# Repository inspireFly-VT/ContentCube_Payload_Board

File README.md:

View this project on [CADLAB.io](https://cadlab.io/project/28566). 

# ContentCube_Payload_Board
The payload board for inspireFly's ContentCube satellite.

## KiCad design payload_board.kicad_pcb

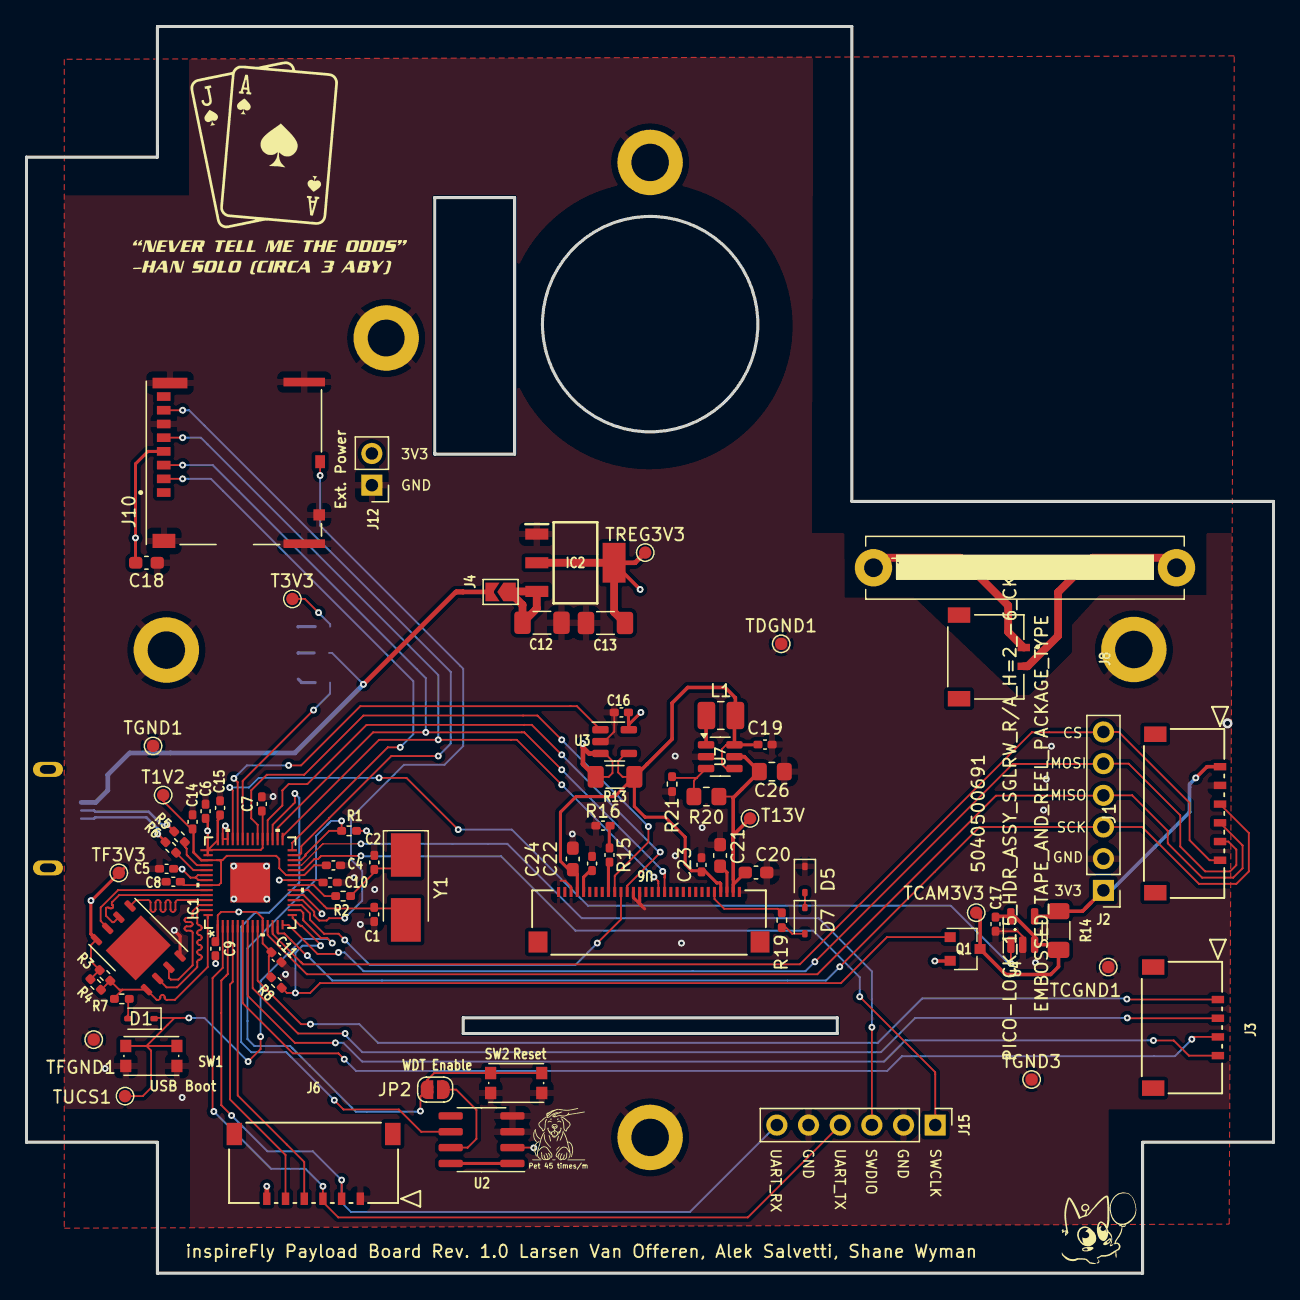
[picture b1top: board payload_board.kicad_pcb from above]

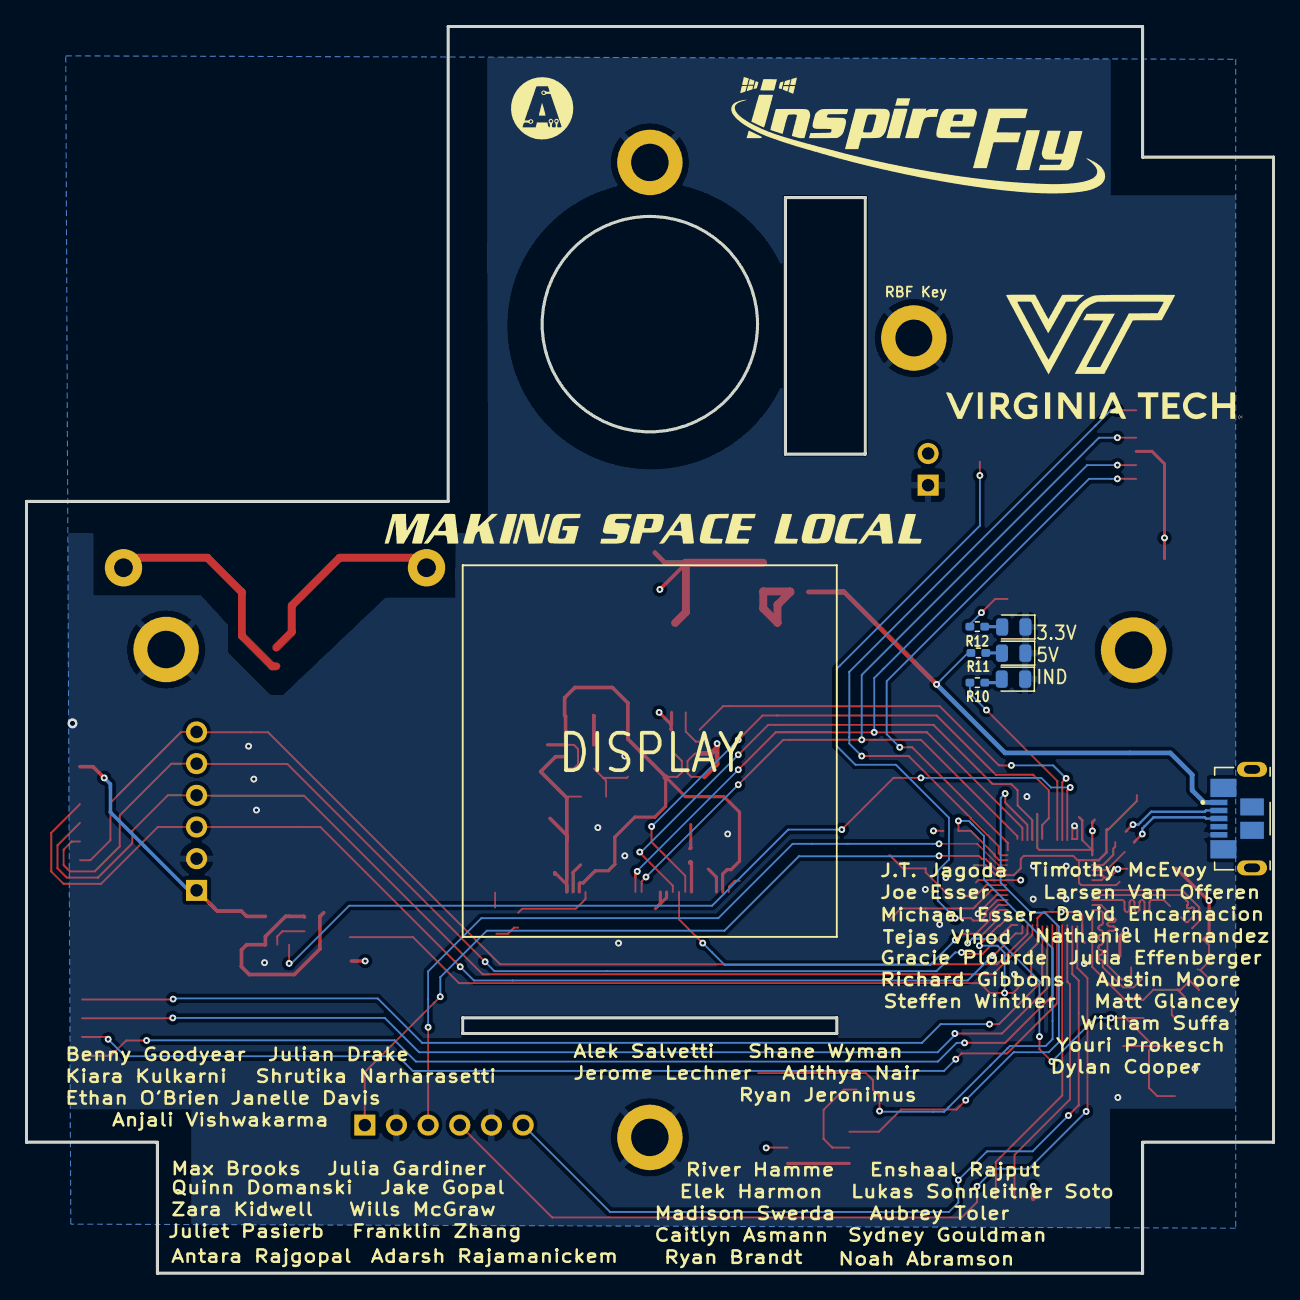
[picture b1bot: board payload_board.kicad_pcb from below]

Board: 4 copper layers, 100.0 x 100.0 mm, 86 parts (8 on the bottom side), 66 nets.

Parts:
C1, C2: 27pF; C_0402_1005Metric_Pad0.74x0.62mm_HandSolder
C4, C5, C7, C8, C9, C10, C11, C15, C16, C17: 0.1uF; C_0402_1005Metric_Pad0.74x0.62mm_HandSolder
C6, C14, C19: 1uF; C_0402_1005Metric_Pad0.74x0.62mm_HandSolder
C12: 10uF; C_1206_3216Metric_Pad1.33x1.80mm_HandSolder
C13: 22uF; C_1206_3216Metric_Pad1.33x1.80mm_HandSolder
C18, C24: 10uF; C_0603_1608Metric_Pad1.08x0.95mm_HandSolder
C20, C21: 10uF/16V; C_0603_1608Metric_Pad1.08x0.95mm_HandSolder
C22, C23: 1.0uF; C_0402_1005Metric_Pad0.74x0.62mm_HandSolder
C26: 4.7uF; R_0805_2012Metric_Pad1.20x1.40mm_HandSolder
D1, D5, D7: NSR0320; D_SOD-323
D2, D3, D4: LED; LED_0805_2012Metric
IC1: RP2040_QFN56; custom_IC57_RP2040
IC2: AZ1117CH-3.3TRG1; SOT230P700X180-4N
J1: Cam_PicoLock; Molex_Pico_CON_5040500691
J2: Cam_Conn; PinHeader_1x06_P2.54mm_Vertical
J2#2, J5: MountingHoles
J3: Antenna_Conn; Molex_Pico_CON_5040500491
J4: usb jumper; SolderJumper-2_P1.3mm_Open_TrianglePad1.0x1.5mm
J6: Breakout; Molex_Pico_CON_5040500691
J7: Molex_Micro_USB; MOLEX_105164-0001
J8: FC to EPS Connector; MOLEX_504050-0291
J10: 503398-1892; MOLEX_503398-1892
J12: FC Breakout; PinHeader_1x02_P2.54mm_Vertical
J15: SWC; PinHeader_1x06_P2.54mm_Vertical
JP2: SolderJumper_2_Open; SolderJumper-2_P1.3mm_Open_RoundedPad1.0x1.5mm
L1: 10uH/1A; L_1008_2520Metric_Pad1.43x2.20mm_HandSolder
Q1: Q_PMOS_GSD; SC-59
R1, R3, R8: 10k; R_0402_1005Metric_Pad0.72x0.64mm_HandSolder
R2, R7: 1K; R_0402_1005Metric_Pad0.72x0.64mm_HandSolder
R4: DNF; R_0402_1005Metric_Pad0.72x0.64mm_HandSolder
R5, R6: 27.4; R_0402_1005Metric_Pad0.72x0.64mm_HandSolder
R10, R12: 220; R_0402_1005Metric_Pad0.72x0.64mm_HandSolder
R11: 470; R_0402_1005Metric_Pad0.72x0.64mm_HandSolder
R13, R14: 0.065; R_1206_3216Metric_Pad1.30x1.75mm_HandSolder
R15, R16: 300k; C_0402_1005Metric_Pad0.74x0.62mm_HandSolder
R19: 50; R_0402_1005Metric_Pad0.72x0.64mm_HandSolder
R20: 16k; R_0805_2012Metric_Pad1.20x1.40mm_HandSolder
R21: 1k; R_0402_1005Metric_Pad0.72x0.64mm_HandSolder
SW1, SW2: KMR2; SW_Push_1P1T_NO_CK_KMR2
T1V2, T3V3, T13V: TESTPOINTROUND1.5MMNO; TestPoint_Pad_D1.0mm
TCAM3V3: TESTPOINTROUND1.5MMNO; TestPoint_Pad_D1.0mm
TCGND1: TESTPOINTROUND1.5MMNO; TestPoint_Pad_D1.0mm
TDGND1: TESTPOINTROUND1.5MMNO; TestPoint_Pad_D1.0mm
TF3V3: TESTPOINTROUND1.5MMNO; TestPoint_Pad_D1.0mm
TFGND1: TESTPOINTROUND1.5MMNO; TestPoint_Pad_D1.0mm
TGND1, TGND3: TESTPOINTROUND1.5MMNO; TestPoint_Pad_D1.0mm
TREG3V3: TESTPOINTROUND1.5MMNO; TestPoint_Pad_D1.0mm
TUCS1: TESTPOINTROUND1.5MMNO; TestPoint_Pad_D1.0mm
U1: W25Q128JVPIQ TR; WDFN-8-1EP_6x5mm_P1.27mm_EP3.4x4mm
U2: MAX706RESA; SOIC-8_3.9x4.9mm_P1.27mm
U3, U4: INA180A3; SOT-23-5
U6: CON30_1X30_DRB_XF2C_TYC
U7: TLV61046ADB; SOT-23-6
Y1: ABLS-12.000MHZ-B2-T; Crystal_SMD_5032-2Pin_5.0x3.2mm_HandSoldering

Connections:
1.2V: C4.2, C5.2, C14.2, IC1.23 (DVDD), IC1.45 (VREG_VOUT), IC1.50 (DVDD), T1V2.1
+3.3V: C6.2, C7.1, C8.1, C9.1, C10.1, C11.1, C13.1, C15.1, C16.1, C18.2, IC1.1 (IOVDD), IC1.10 (IOVDD), IC1.22 (IOVDD), IC1.33 (IOVDD), IC1.42 (IOVDD), IC1.43 (ADC_IOVDD), IC1.44 (VREG_IOVDD), IC1.48 (USB_IOVDD), IC1.49 (IOVDD), IC2.2 (OUTPUT), IC2.4 (VOUT), J6.6, J10.4 (VDD), J12.2, Q1.2 (S), R1.1, R3.1, R4.2, R8.2, R12.2, R13.2, T3V3.1, TF3V3.1, TREG3V3.1, U1.8 (VCC), U2.2 (VCC), U3.3 (+), U3.5 (V+)
+13V: C20.2, C26.2, R20.1, T13V.1, U6.P$29 (VCC), U7.5 (VOUT)
/D+: J7.3 (D+), R6.1
/D-: J7.2 (D-), R5.2
/QSPI_CS: IC1.56 (~QSPI_CS), R3.2, R4.1, R7.1, U1.1 (SSEL)
/QSPI_DATA[0]: IC1.53 (QSPI_SD0), U1.5 (MOSI)
/QSPI_DATA[1]: IC1.55 (QSPI_SD1), U1.2 (MISO)
/QSPI_DATA[2]: IC1.54 (QSPI_SD2), U1.3 (WP#/IO2)
/QSPI_DATA[3]: IC1.51 (QSPI_SD3), U1.7 (HOLD#/IO3)
/QSPI_SCK: IC1.52 (QSPI_SCLK), U1.6 (SCK)
/USBBOOT: D1.1 (C), IC1.16 (GPIO13), SW1.1, TUCS1.1
/~RESET: IC1.26 (/RUN), JP2.2 (B), R1.2, SW2.1
ADC0: IC1.38 (GPIO26/AD0), U3.1
ADC1: IC1.39 (GPIO27/AD1), U4.1
BURN_A: IC1.8 (GPIO6), J3.2
BURN_B: IC1.9 (GPIO7), J3.1
Break_SCL: IC1.5 (GPIO3), J6.4
Break_SDA: IC1.4 (GPIO2), J6.5
CIN-: J1.1, J2.1, R14.2, U4.4 (-)
Cam_3.3v: C17.2, Q1.3 (D), R14.1, TCAM3V3.1, U4.3 (+), U4.5 (V+)
Cam_RST: IC1.15 (GPIO12), Q1.1 (G), R8.1
DIN-: C19.2, C23.2, C24.2, L1.1, R13.1, U3.4 (-), U6.P$4 (VCI), U6.P$27 (VDDIO), U7.4 (EN), U7.6 (VI)
Disp_DC: IC1.17 (GPIO14), U6.P$11 (D/C#)
Disp_RST: IC1.34 (GPIO22), U6.P$10 (RES#)
GND: C1.1, C2.1, C4.1, C5.1, C6.1, C7.2, C8.2, C9.2, C10.2, C11.2, C12.2, C13.2, C14.1, C15.2, C16.2, C17.1, C18.1, C19.1, C20.1, C21.1, C22.1, C23.1, C24.1, C26.1, D2.1 (K), D3.1 (K), D4.1 (K), D5.1 (C), IC1.19 (TESTEN), IC1.40 (GPIO28/AD2), IC1.41 (GPIO29/AD3), IC1.57, IC2.1 (ADJ/GND), J1.2, J2.2, J2#2.1 (VTref), J5.1, J6.1, J7.5 (GND), J10.6 (VSS), J10.9 (VSS__1), J10.P1 (SHIELD), J10.P2 (SHIELD__1), J10.P3 (SHIELD__2), J10.P4 (SHIELD__3), J12.1, J15.2, J15.5, R16.1, R21.2, SW1.2 (S), SW2.2 (S1), TCGND1.1, TDGND1.1, TFGND1.1, TGND1.1, TGND3.1, U1.4 (VSS), U2.3 (GND), U2.4 (PFI), U3.2 (GND), U4.2 (GND), U6.P$1 (NC(GND)@2), U6.P$3 (VSS), U6.P$13 (BS1), U6.P$14 (BS0), U6.P$30 (NC(GND)@1), U7.2 (GND)
I2C1_SCL: IC1.7 (GPIO5), J3.4
I2C1_SDA: IC1.6 (GPIO4), J3.3
unnamed: C2.2, R2.1, Y1.1
unnamed: D1.2 (A), R7.2
unnamed: D2.2 (A), R10.1
unnamed: D3.2 (A), R11.1
unnamed: D4.2 (A), R12.1
unnamed: D5.2 (A), D7.1 (C)
unnamed: D7.2 (A), R19.1
unnamed: IC1.37 (GPIO25), R10.2
unnamed: IC1.47 (USB_D+), R6.2
unnamed: IC1.46 (USB_D-), R5.1
unnamed: C1.2, IC1.20 (XIN), Y1.2
unnamed: IC1.21 (XOUT), R2.2
unnamed: JP2.1 (A), U2.7 (~RESET)
unnamed: R15.1, R16.2
unnamed: U2.1 (~MR), U2.8 (~WDO)
unnamed: R15.2, U6.P$9 (IREF)
unnamed: C21.2, U6.P$28 (VCOMH)
unnamed: C22.2, U6.P$5 (VDD)
unnamed: R19.2, U6.P$26 (VSL)
unnamed: R20.2, R21.1, U7.3 (FB)
unnamed: L1.2, U7.1 (SW)
SD_IND: IC1.18 (GPIO15), J10.10 (DETECT_SWITCH)
SPI0_CS_DISP: IC1.32 (GPIO21), U6.P$12 (CS#)
SPI0_CS_SD: IC1.28 (GPIO17), J10.2 (CD/DAT3^2)
SPI0_MISO: IC1.27 (GPIO16), J10.7 (DAT0)
SPI0_MOSI: IC1.30 (GPIO19), J10.3 (CMD), U6.P$18 (D1/SDIN)
SPI0_SCK: IC1.29 (GPIO18), J10.5 (CLK), U6.P$17 (D0/SCK)
SPI1_CS_Cam: IC1.12 (GPIO9), J1.6, J2.6
SPI1_MISO_Cam: IC1.11 (GPIO8), J1.4, J2.4
SPI1_MOSI_Cam: IC1.14 (GPIO11), J1.5, J2.5
SPI1_SCK_Cam: IC1.13 (GPIO10), J1.3, J2.3
SWCLK: IC1.24 (SWCLK), J15.1
SWDIO: IC1.25 (SWDIO), J15.3
UART1_RX: IC1.3 (GPIO1), J6.2, J15.6
UART1_TX: IC1.2 (GPIO0), J6.3, J15.4
VBUS: J4.2 (B), J7.1 (VBUS), R11.2
VUR: C12.1, IC2.3 (INPUT), J4.1 (A)
WDT_WDI: IC1.31 (GPIO20), U2.6 (~WDI)

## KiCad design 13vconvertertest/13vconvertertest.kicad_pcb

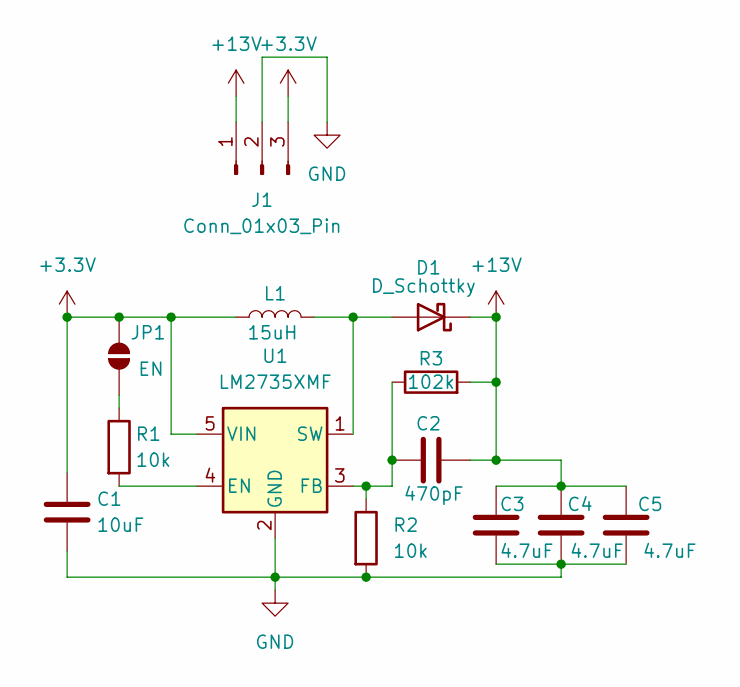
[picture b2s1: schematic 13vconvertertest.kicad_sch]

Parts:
C1: 10uF; C_0402_1005Metric
C2: 470pF; C_0805_2012Metric
C3, C4, C5: 4.7uF; C_0603_1608Metric
D1: D_Schottky; D_SOD-123F
J1: Conn_01x03_Pin; PinHeader_1x03_P1.00mm_Vertical
JP1: EN; SolderJumper-2_P1.3mm_Open_TrianglePad1.0x1.5mm
L1: 15uH; L_Bourns-SRU1028_10.0x10.0mm
R1, R2: 10k; R_0805_2012Metric
R3: 102k; R_0402_1005Metric
U1: LM2735XMF; SOT-23-5

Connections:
+3.3V: C1.1, J1.3, JP1.2 (B), L1.1, U1.5 (VIN)
+13V: C2.2, C3.1, C4.1, C5.1, D1.1 (K), J1.1, R3.2
GND: C1.2, C3.2, C4.2, C5.2, J1.2, R2.2, U1.2 (GND)
unnamed: D1.2 (A), L1.2, U1.1 (SW)
unnamed: JP1.1 (A), R1.1
unnamed: R1.2, U1.4 (EN)
unnamed: C2.1, R2.1, R3.1, U1.3 (FB)

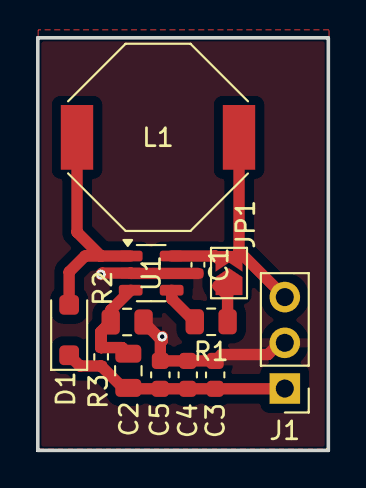
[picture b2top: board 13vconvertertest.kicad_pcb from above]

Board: 2 copper layers, 16.1 x 22.9 mm, 13 parts (0 on the bottom side), 7 nets.

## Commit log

2024-10-15 Port from CADLAB to Github
2024-10-15 Backlink to CADLAB.io has been added.
2024-10-16 Updated component placements and footprints
2024-10-17 Updated display footprints to reflect avaliability
2024-10-19 Changed the orientation of the connector to align, and moved a couple of the components Will continue tomorrow
2024-10-19 Forgot to save changes for schematic
2024-10-19 Rotated it back (by bad i dont know how to read schematics) and added some connections
2024-10-19 Connected some more stuff
2024-10-20 Moved the sd card on the board
2024-10-20 oops, forgot to connect some of the gnd pins
2024-10-20 Some of the planes where unconnected
2024-10-20 Moved some of the traces further appart
2024-10-20 A little more
2024-10-20 Final move
2024-10-20 moved some of the silkcreen labels
2024-10-20 Moved some line appart
2024-10-20 Inventory of the components
2024-10-23 Fixed RP2040 connections and changed sd card
2024-10-23 changed footprint for sd card and fixed not gnd planes
2024-10-23 Fixed some errors and added manufactering file
2024-10-25 Update BOM and part identifiers on PCB
2024-10-26 Updated inventory (payload_board.xlsx)
2024-10-27 Updated footprints
2024-10-28 Finalized part selection and gbr for 073 manufacturing.
2024-10-31 Flipped the outline and moved the screen and some of the connectors Now the front in Kicad is the back in the satelite (inside) and vice versa
2024-11-01 Moved the final connector from back to front, footprint kepout for chasis mounts and moved sd card
2024-11-03 Changed some components to decrease bom count (C18, C25)
2024-11-03 Add JLC Part identifiers
2024-11-05 Updated footprints to reduce part count.
2024-11-05 flipped camera power monitor and reset
2024-11-08 stuck with new buck converter Trying to understand why BOOT is limited to 10 V, even if output is supposed to be 14V
2024-11-09 Update for JLC PCBA part selection
2024-11-09 Added new 13V boost converter
2024-11-10 Added .gitignore for Kicad temp files and updated bom for JLC parts
2024-11-10 Added .gitignore to remove JLC temp files
2024-11-14 Update placement blocking connectors
2024-11-16 Updated footprints to refelct part avaliability
2024-11-17 Changed BOM to refelct part avaliability
2024-11-18 Change part selection to reflect avaliability
2024-12-05 Added alternative 13v regulator setup for testing
2024-12-06 Updated Some placements and DNP flags for manu.
2024-12-08 Fixed some unconected traces
2024-12-08 Modified the 13V booster planes
2024-12-08 Switched to cleaner circle
2025-01-23 Fixed the RP2040 Ground Pad
2025-01-23 Moved ribbon hole by 0.8 mm down
2025-01-23 Added display footprint
2025-01-29 Updated logos and symbols
2025-01-30 Removed lock file
2025-02-02 Updated Graphics
2025-02-03 Updated files for manufacturing
2025-02-03 Updated for v1.0 manufacturing
2025-02-07 Updated for manufacturing
2025-02-12 added connector diagram
2025-02-18 added meme
